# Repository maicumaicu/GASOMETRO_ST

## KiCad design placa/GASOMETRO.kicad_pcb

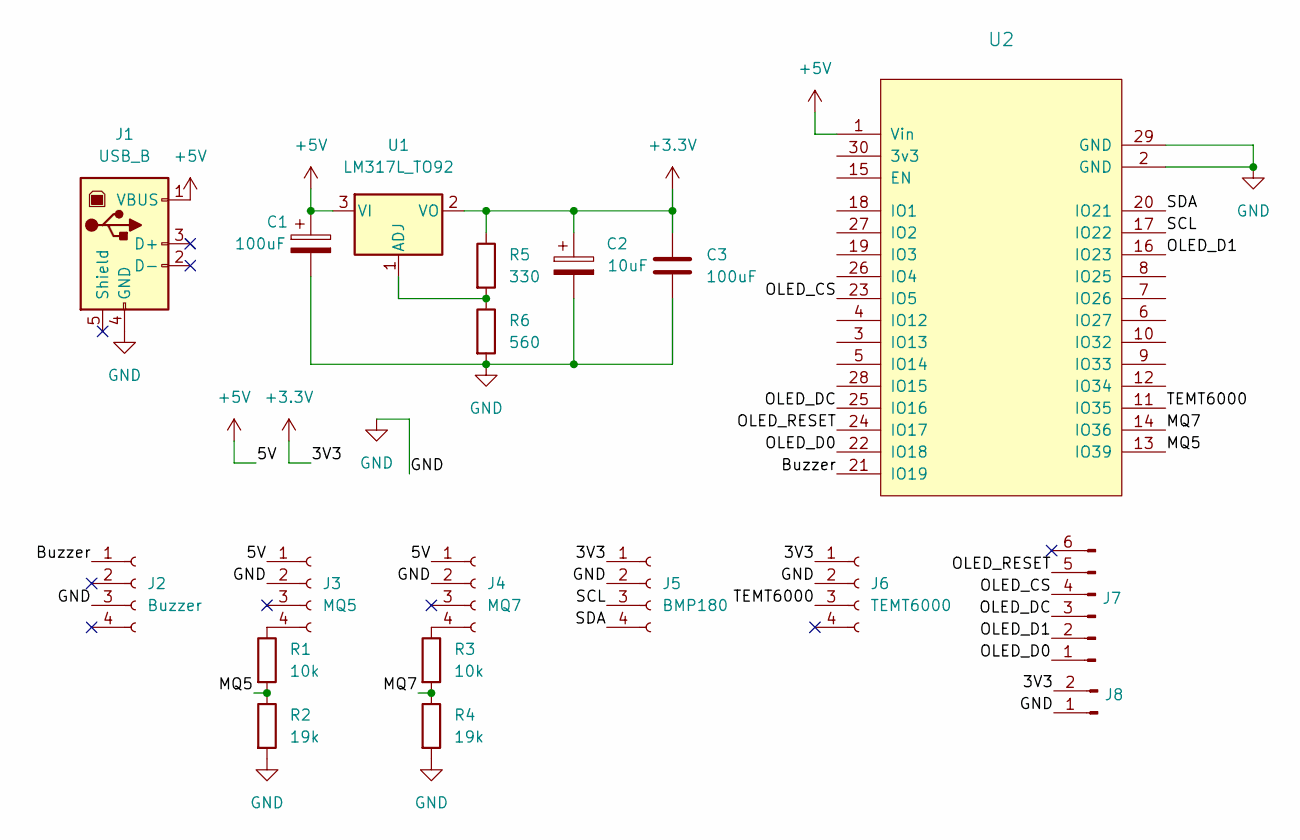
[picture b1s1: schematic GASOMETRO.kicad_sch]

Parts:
C1, C3: 100uF
C2: 10uF
J1: USB_B
J2: Buzzer
J3: MQ5
J4: MQ7
J5: BMP180
J6: TEMT6000
J7, J8: (no value)
R1, R3: 10k
R2, R4: 19k
R5: 330
R6: 560
U1: LM317L_TO92; TO-92_Inline
U2: (no value)

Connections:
+3V3: C2.1, C3.1, J5.1, J6.1, J8.2, R5.1, U1.2 (VO)
+5V: C1.1, J1.1 (VBUS), J3.1, J4.1, U1.3 (VI), U2.1 (Vin)
/Buzzer: J2.1, U2.21 (IO19)
/MQ5: R1.2, R2.1, U2.13 (IO39)
/MQ7: R3.2, R4.1, U2.14 (IO36)
/OLED_CS: J7.4, U2.23 (IO5)
/OLED_D0: J7.1, U2.22 (IO18)
/OLED_D1: J7.2, U2.16 (IO23)
/OLED_DC: J7.3, U2.25 (IO16)
/OLED_RESET: J7.5, U2.24 (IO17)
/SCL: J5.3, U2.17 (IO22)
/SDA: J5.4, U2.20 (IO21)
/TEMT6000: J6.3, U2.11 (IO35)
GND: C1.2, C2.2, C3.2, J1.4 (GND), J2.3, J3.2, J4.2, J5.2, J6.2, J8.1, R2.2, R4.2, R6.2, U2.2 (GND), U2.29 (GND)
unnamed: J3.4, R1.1
unnamed: J4.4, R3.1
unnamed: R5.2, R6.1, U1.1 (ADJ)

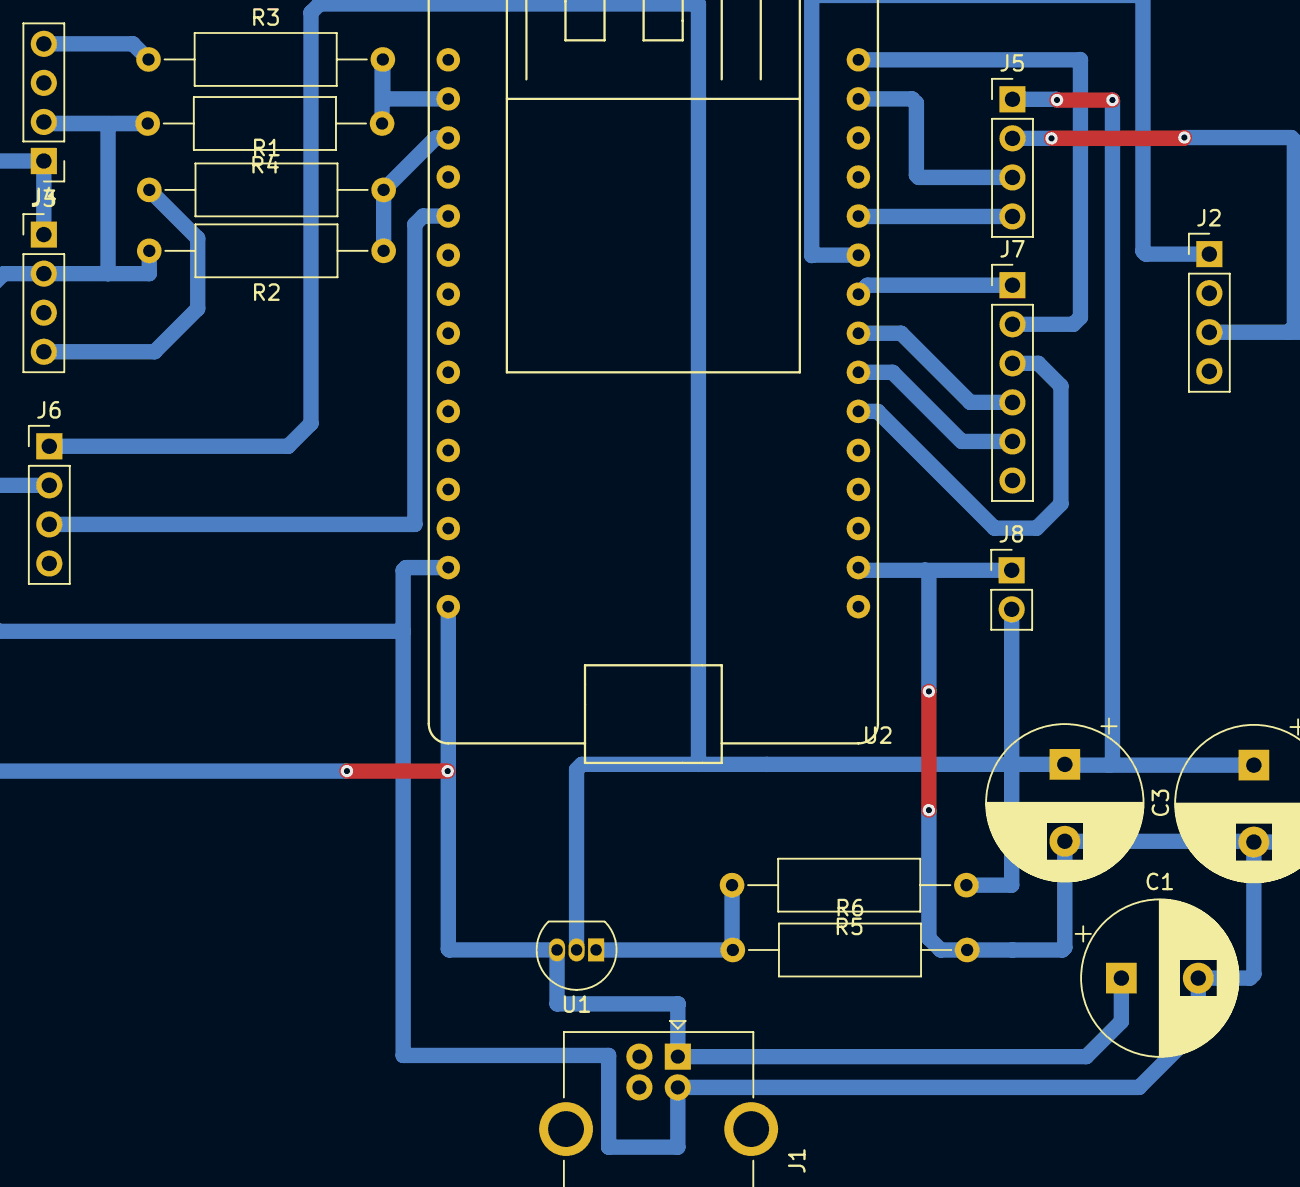
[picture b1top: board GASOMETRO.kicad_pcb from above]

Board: 2 copper layers, 19 parts (0 on the bottom side), 17 nets.

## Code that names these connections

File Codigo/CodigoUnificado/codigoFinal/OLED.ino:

#include <SPI.h>
#include <Wire.h>
#include <Adafruit_GFX.h>
#include <Adafruit_SSD1306.h>

#define SCREEN_WIDTH 128
#define SCREEN_HEIGHT 64

#define OLED_D1   23
#define OLED_D0    18
#define OLED_DC     16
#define OLED_CS     5
#define OLED_RESET  17

Adafruit_SSD1306 display(SCREEN_WIDTH, SCREEN_HEIGHT,
                         OLED_D1, OLED_D0, OLED_DC, OLED_RESET, OLED_CS);


bool setupOLED()
{
  if (!display.begin(SSD1306_SWITCHCAPVCC))
  {
    Serial.println(F("SSD1306 allocation failed"));
    return false;
  }
  Serial.println(F("correcto"));
  display.clearDisplay();
  display.display();
  return true;
}

void EmergencyState(int* values) {

}
void cDisplay() {
  display.clearDisplay();
}


void displayData(int *values) {
  DisplayBMP180(values[BMP180]);
  DisplayMQ7(values[MQ7]);
  DisplayMQ5(values[MQ5]);
  DisplayTEMT6000(values[TEMT6000]);
}

void DisplayBMP180(int value) {
  //display.clearDisplay();
  display.setTextSize(1);
  display.setTextColor(SSD1306_WHITE);
  display.setCursor(1, 28);
  display.print("BMP: ");
  if (value == -1) {
    display.println("No disponible");
  } else {
    display.println(value);
  }
  display.display();
}

void DisplayMQ5(int value) {
  display.setTextSize(1);
  display.setTextColor(SSD1306_WHITE);
  //display.setCursor(6, 28);
  display.print("MQ5: ");
  display.println(value);
  display.display();
}

void DisplayMQ7(int value) {
  display.setTextSize(1);
  display.setTextColor(SSD1306_WHITE);
  //display.setCursor(7, 28);
  display.print("MQ7: ");
  display.println(value);
  display.display();
}

void DisplayTEMT6000(int value) {
  display.setTextSize(1);
  display.setTextColor(SSD1306_WHITE);
  //display.setCursor(8, 28);
  display.print("TEMT: ");
  display.println(value);
  display.display();
}

/*void AllPixels()
  {
  int i;
  int j;
  display.clearDisplay();
  for (i = 0; i < 64; i++)
  {
    for (j = 0; j < 128; j++)
    {
      display.drawPixel(j, i, SSD1306_WHITE);

    }
    display.display();
    delay(30);
  }

  for (i = 0; i < 64; i++)
  {
    for (j = 0; j < 128; j++)
    {
      display.drawPixel(j, i, SSD1306_BLACK);

    }
    display.display();
    delay(30);
  }

  }

  void TextDisplay()
  {
  display.clearDisplay();
  display.setTextSize(1);
  display.setTextColor(SSD1306_WHITE);
  display.setCursor(5, 28);
  display.println("Electronics Hub");
  display.display();
  delay(3000);
  }

  void InvertedTextDisplay()
  {
  display.clearDisplay();
  display.setTextColor(SSD1306_BLACK, SSD1306_WHITE);
  display.setCursor(5, 28);
  display.println("Electronics Hub");
  display.display();
  delay(3000);
  }

  void ScrollText()
  {
  display.clearDisplay();
  display.setCursor(0, 0);
  display.setTextSize(1);
  display.setTextColor(SSD1306_WHITE);
  display.println("This is a");
  display.println("Scrolling");
  display.println("Text!");
  display.display();
  delay(100);
  display.startscrollright(0x00, 0x0F);
  delay(2000);
  //display.stopscroll();
  //delay(1000);
  display.startscrollleft(0x00, 0x0F);
  delay(2000);
  //display.stopscroll();
  //delay(1000);
  display.startscrolldiagright(0x00, 0x0F);
  delay(2000);
  display.startscrolldiagleft(0x00, 0x0F);
  delay(2000);
  display.stopscroll();
  }

  void DisplayChars()
  {
  display.clearDisplay();

  display.setTextSize(1);
  display.setTextColor(SSD1306_WHITE);
  display.setCursor(0, 0);
  display.cp437(true);

  for (int16_t i = 0; i < 256; i++)
  {
    if (i == '\n')
    {
      display.write(' ');
    }
    else
    {
      display.write(i);
    }
  }

  display.display();
  delay(4000);
  }
  void TextSize()
  {
  display.clearDisplay();

  display.setTextSize(1);
  display.setTextColor(SSD1306_WHITE);
  display.setCursor(0, 0);
  display.println(F("Size: 1"));
  display.println(F("ABC"));

  display.setTextSize(2);
  display.setTextColor(SSD1306_WHITE);
  display.println("Size: 2");
  display.println(F("ABC"));

  display.display();
  delay(3000);
  }

  void DrawRectangle()
  {
  display.clearDisplay();
  display.setTextSize(1);
  display.setTextColor(WHITE);
  display.setCursor(0, 0);
  display.println("Rectangle");
  display.drawRect(0, 15, 90, 45, SSD1306_WHITE);
  display.display();
  delay(2000);
  }

  void DrawFilledRectangle()
  {
  display.clearDisplay();
  display.setTextSize(1);
  display.setTextColor(WHITE);
  display.setCursor(0, 0);
  display.println("Filled Rectangle");
  display.fillRect(0, 15, 90, 45, SSD1306_WHITE);
  display.display();
  delay(2000);

  }

  void DrawRoundRectangle()
  {
  display.clearDisplay();
  display.setTextSize(1);
  display.setTextColor(SSD1306_WHITE);
  display.setCursor(0, 0);
  display.println("Round Rectangle");
  display.drawRoundRect(0, 15, 90, 45, 10, SSD1306_WHITE);
  display.display();
  delay(2000);
  }

  void DrawFilledRoundRectangle()
  {
  display.clearDisplay();
  display.setTextSize(1);
  display.setTextColor(SSD1306_WHITE);
  display.setCursor(0, 0);
  display.println("Filled Round Rect");
  display.fillRoundRect(0, 15, 90, 45, 10, SSD1306_WHITE);
  display.display();
  delay(2000);

  }

  void DrawCircle()
  {
  display.clearDisplay();
  display.setTextSize(1);
  display.setTextColor(SSD1306_WHITE);
  display.setCursor(0, 0);
  display.println("Circle");
  display.drawCircle(30, 36, 25, SSD1306_WHITE);
  display.display();
  delay(2000);
  }
  void DrawFilledCircle()
  {
  display.clearDisplay();
  display.setTextSize(1);
  display.setTextColor(SSD1306_WHITE);
  display.setCursor(0, 0);
  display.println("Filled Circle");
  display.fillCircle(30, 36, 25, SSD1306_WHITE);
  display.display();
  delay(2000);

  }

  void DrawTriangle()
  {
  display.clearDisplay();
  display.setTextSize(1);
  display.setTextColor(SSD1306_WHITE);
  display.setCursor(0, 0);
  display.println("Triangle");
  display.drawTriangle(30, 15, 0, 60, 60, 60, SSD1306_WHITE);
  display.display();
  delay(2000);
  }

  void DrawFilledTriangle()
  {
  display.clearDisplay();
  display.setTextSize(1);
  display.setTextColor(SSD1306_WHITE);
  display.setCursor(0, 0);
  display.println("Filled Triangle");
  display.fillTriangle(30, 15, 0, 60, 60, 60, SSD1306_WHITE);
  display.display();
  delay(2000);
  }
*/

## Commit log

2022-07-09 armo casi todo
2022-08-31 fdgdf
2022-09-13 dgfg
